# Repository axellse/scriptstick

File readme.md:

# scriptstick

The scriptstick is a versatile scripting device in the form of a usb flash drive. It is very similar to the traditional badusb, but since it uses Lua instead of DuckyScript, it can do so much more than act as a keyboard. The onboard hardware also allows for things like meshtastic. The firmware writen in go with tinygo.

## why?

I made this project because i love the form factor of a usb stick, and i felt that a lot of fun could be had by expanding the capabilities of traditional bad usbs to more than just HID. By adding just a couple of hardware components you can make a regular looking usb stick so incredily versatile. Pair this with being able to change function easily through a dip switch and you've got yourself a swiss army knife for computers. (holy phone salesman)

## how?
I have compiled a couple examples of what the scriptstick could do (theoretically, since i dont have the device yet):
- badusb (ofc)
- security key where the private keys are stored on an sd card which you could hide somewhere.
- boot a very small OS (in theory)
- IR LED to MOSFET pads + usb otg adapter + android phone + custom app = portable universal tv remote
- meshtastic!!! on the go maybe with an android phone?
- communicate with another scriptstick up to kilometers away!
- sd card to usb adapter (not the fastest)
- not sure if mosfets have any/enough capacitance to make this not work but you could build a pretty shitty mp3 player.
- modify a keyboard with a lora module inside, plug scriptstick into your pc, use your keyboard from kilometers away. (why)

The scriptstick project is sponsored by [Hack club](https://hack.club).

## blueprint approval stuff
### schematic

### pcb

### BOM
|Name                   |Quantity|Unit cost (SEK)|Variant                    |Manufacturer/seller    |Cost (SEK)|Link                       |Comment                                                  |
|-----------------------|--------|---------------|---------------------------|-----------------------|----------|---------------------------|---------------------------------------------------------|
|USB C to A adapter     |1       |22,17          |Blue A to C                |Elough Store/Aliexpress|22,17     |[Link](https://www.aliexpress.com/item/1005008596972414.html)                   |Required as my PC only has USB A and not C               |
|Components             |3       |134,67         |N/A                        |LCSC                   |404,01    |N/A (Private shopping cart)|See production/lcsc_bom.csv in the git repo              |
|LCSC Shipping Fee      |N/A     |N/A            |Global Direct Standard Line|LCSC                   |91,75     |N/A                        |                                                         |
|PCBs                   |10      |4,73           |Black 2-layer              |JLCPCB                 |47,3      |N/A (Private shopping cart)|See production/gerber.zip in the git repo.               |
|PCB Stencil            |1       |108,42         |Top+Bottom on same stencil |JLCPCB                 |108,42    |N/A (Private shopping cart)|I assemble myself to minimize costs                      |
|JLCPCB Shipping Fee    |N/A     |N/A            |Global Direct Standard Line|JLCPCB                 |179,73    |N/A                        |                                                         |
|Aliexpress Shipping Fee|N/A     |N/A            |Choice shipping (cheapest) |Aliexpress             |18,68     |N/A                        |                                                         |

|Total (SEK)            |N/A|N/A   |N/A                        |N/A                    |872,06|N/A                        |Note that Swedish 25% sales tax is included in all prices|
|-----------------------|---|------|---------------------------|-----------------------|------|---------------------------|---------------------------------------------------------|
|Total (USD): 95$       |   |      |                           |                       |      |                           |                                                         |

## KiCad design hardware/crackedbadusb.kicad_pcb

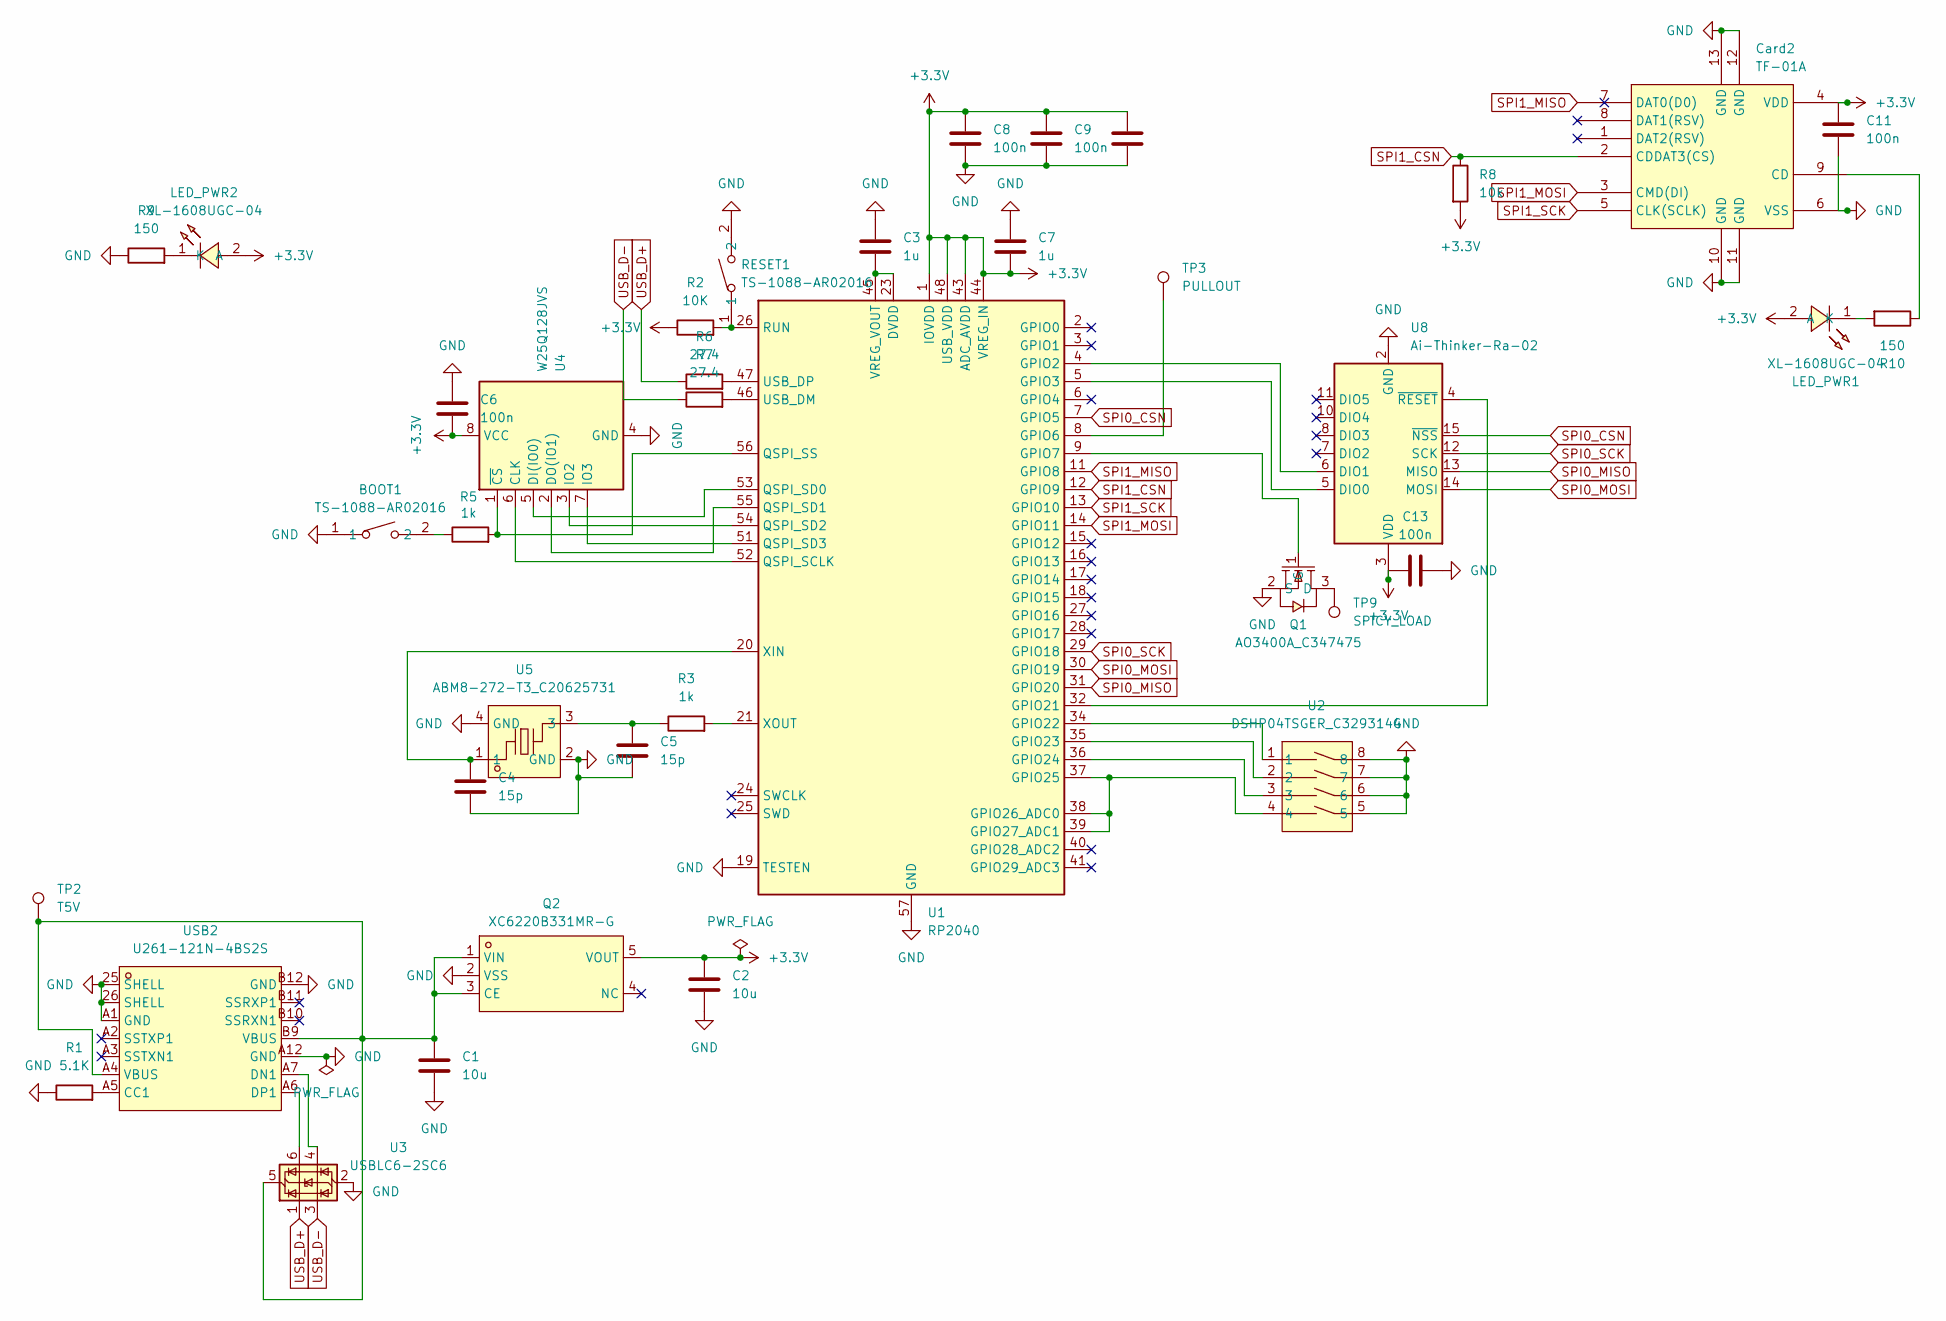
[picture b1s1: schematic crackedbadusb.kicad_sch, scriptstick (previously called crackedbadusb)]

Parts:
BOOT1: TS-1088-AR02016; SW-SMD_L3.9-W3.0-P4.45; LCSC Part C720477
C1, C2: 10u; C_0603_1608Metric
C3, C7: 1u; C_0603_1608Metric
C4, C5: 15p; C_0603_1608Metric
C6, C8, C9, C10, C11, C13: 100n; C_0603_1608Metric
Card2: TF-01A; TF-SMD_TF-01A; LCSC Part C91145
LED_PWR1, LED_PWR2: XL-1608UGC-04; LED0603-RD_GREEN; LCSC Part C965804
Q1: AO3400A_C347475; SOT-23-3_L2.9-W1.3-P1.90-LS2.4-BR; LCSC Part C347475
Q2: XC6220B331MR-G; SOT-25_L3.0-W1.6-P0.95-LS2.8-TL; LCSC Part C86534
R1: 5.1K; R_0603_1608Metric
R2: 10K; R_0603_1608Metric
R3, R5: 1k; R_0603_1608Metric
R6, R7: 27.4; R_0603_1608Metric
R8: 10k; R_0603_1608Metric
R9, R10: 150; R_0603_1608Metric
RESET1: TS-1088-AR02016; SW-SMD_L3.9-W3.0-P4.45; LCSC Part C720477
TP2: T5V; TestPoint_Pad_D2.0mm
TP3: PULLOUT; TestPoint_Pad_D2.5mm
TP9: SPICY_LOAD; TestPoint_Pad_D2.5mm
U1: RP2040; QFN-56-1EP_7x7mm_P0.4mm_EP3.2x3.2mm
U2: DSHP04TSGER_C3293144; SW-SMD_8P-L6.7-W5.4-P1.27-LS8.4; LCSC Part C3293144
U3: USBLC6-2SC6; SOT-23-6
U4: W25Q128JVS; SOIC-8_5.23x5.23mm_P1.27mm
U5: ABM8-272-T3_C20625731; CRYSTAL-SMD_4P-L3.2-W2.5-BL; LCSC Part C20625731
U8: Ai-Thinker-Ra-02; Ai-Thinker-Ra-01-LoRa
USB2: U261-121N-4BS2S; USB-C-SMD_U261-121N-4BS2S; LCSC Part C2879827

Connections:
+3.3V: C2.1, C6.2, C7.2, C8.1, C9.1, C10.1, C11.1, C13.1, Card2.4 (VDD), LED_PWR1.2 (A), LED_PWR2.2 (A), Q2.5 (VOUT), R2.1, R8.2, U1.1 (IOVDD), U1.10 (IOVDD), U1.22 (IOVDD), U1.33 (IOVDD), U1.42 (IOVDD), U1.43 (ADC_AVDD), U1.44 (VREG_IN), U1.48 (USB_VDD), U1.49 (IOVDD), U4.8 (VCC), U8.3 (VDD)
GND: BOOT1.1, C1.2, C2.2, C3.1, C4.2, C5.2, C6.1, C7.1, C8.2, C9.2, C10.2, C11.2, C13.2, Card2.6 (VSS), Card2.10 (GND), Card2.11 (GND), Card2.12 (GND), Card2.13 (GND), Q1.2 (S), Q2.2 (VSS), R1.1, R9.1, RESET1.2, U1.19 (TESTEN), U1.57 (GND), U2.5, U2.6, U2.7, U2.8, U3.2 (GND), U4.4 (GND), U5.2 (GND), U5.4 (GND), U8.1 (GND), U8.2 (GND), U8.9 (GND), U8.16 (GND), USB2.25 (SHELL), USB2.26 (SHELL), USB2.A1 (GND), USB2.A12 (GND), USB2.B12 (GND)
unnamed: BOOT1.2, R5.1
unnamed: C5.1, R3.1, U5.3
unnamed: Card2.9 (CD), R10.1
unnamed: LED_PWR1.1 (K), R10.2
unnamed: LED_PWR2.1 (K), R9.2
unnamed: Q1.3 (D), TP9.1
unnamed: Q1.1 (G), U1.9 (GPIO7)
unnamed: C1.1, Q2.1 (VIN), Q2.3 (CE), TP2.1, U3.5 (VBUS), USB2.A4 (VBUS), USB2.B9 (VBUS)
unnamed: U1.4 (GPIO2), U8.6 (DIO1)
unnamed: U1.5 (GPIO3), U8.5 (DIO0)
unnamed: TP3.1, U1.8 (GPIO6)
unnamed: U1.32 (GPIO21), U8.4 (~RESET)
unnamed: U1.34 (GPIO22), U2.1
unnamed: U1.35 (GPIO23), U2.2
unnamed: U1.36 (GPIO24), U2.3
unnamed: U1.37 (GPIO25), U1.38 (GPIO26_ADC0), U1.39 (GPIO27_ADC1), U2.4
unnamed: U1.52 (QSPI_SCLK), U4.6 (CLK)
unnamed: U1.53 (QSPI_SD0), U4.5 (DI(IO0))
unnamed: U1.55 (QSPI_SD1), U4.2 (DO(IO1))
unnamed: U1.54 (QSPI_SD2), U4.3 (IO2)
unnamed: U1.51 (QSPI_SD3), U4.7 (IO3)
unnamed: R5.2, U1.56 (QSPI_SS), U4.1 (~CS)
unnamed: R2.2, RESET1.1, U1.26 (RUN)
unnamed: R7.2, U1.46 (USB_DM)
unnamed: R6.2, U1.47 (USB_DP)
unnamed: C3.2, U1.23 (DVDD), U1.45 (VREG_VOUT), U1.50 (DVDD)
unnamed: C4.1, U1.20 (XIN), U5.1
unnamed: R3.2, U1.21 (XOUT)
unnamed: R1.2, USB2.A5 (CC1)
unnamed: U3.4 (I/O2), USB2.A7 (DN1)
unnamed: U3.6 (I/O1), USB2.A6 (DP1)
SPI0_CSN: U1.7 (GPIO5), U8.15 (~NSS)
SPI0_MISO: U1.31 (GPIO20), U8.13 (MISO)
SPI0_MOSI: U1.30 (GPIO19), U8.14 (MOSI)
SPI0_SCK: U1.29 (GPIO18), U8.12 (SCK)
SPI1_CSN: Card2.2 (CDDAT3(CS)), R8.1, U1.12 (GPIO9)
SPI1_MISO: Card2.7 (DAT0(D0)), U1.11 (GPIO8)
SPI1_MOSI: Card2.3 (CMD(DI)), U1.14 (GPIO11)
SPI1_SCK: Card2.5 (CLK(SCLK)), U1.13 (GPIO10)
USB_D+: R6.1, U3.1 (I/O1)
USB_D-: R7.1, U3.3 (I/O2)

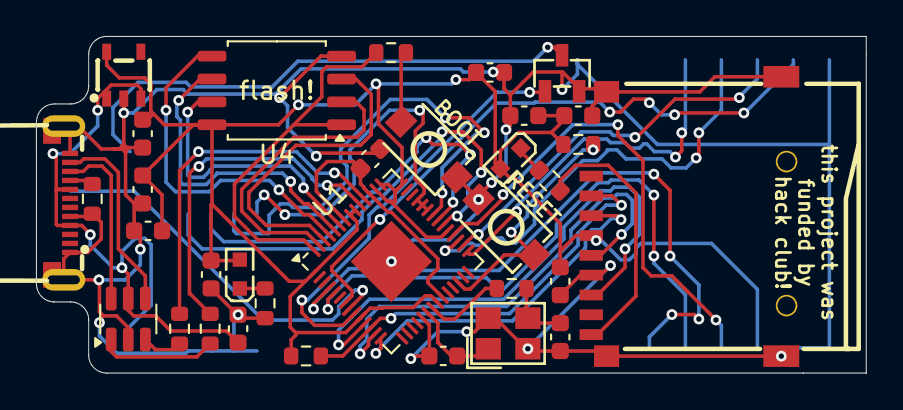
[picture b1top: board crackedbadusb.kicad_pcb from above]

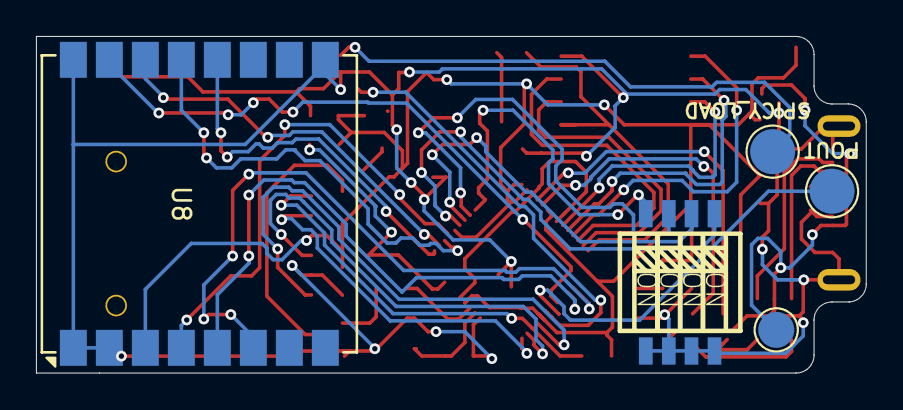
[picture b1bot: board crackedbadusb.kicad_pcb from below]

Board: 2 copper layers, 46.1 x 18.7 mm, 38 parts (5 on the bottom side), 43 nets.

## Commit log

2026-01-13 blueprint compliance stuff
2026-01-13 remove section of readme
2026-01-13 more readme stuff
2026-01-19 typo fix
